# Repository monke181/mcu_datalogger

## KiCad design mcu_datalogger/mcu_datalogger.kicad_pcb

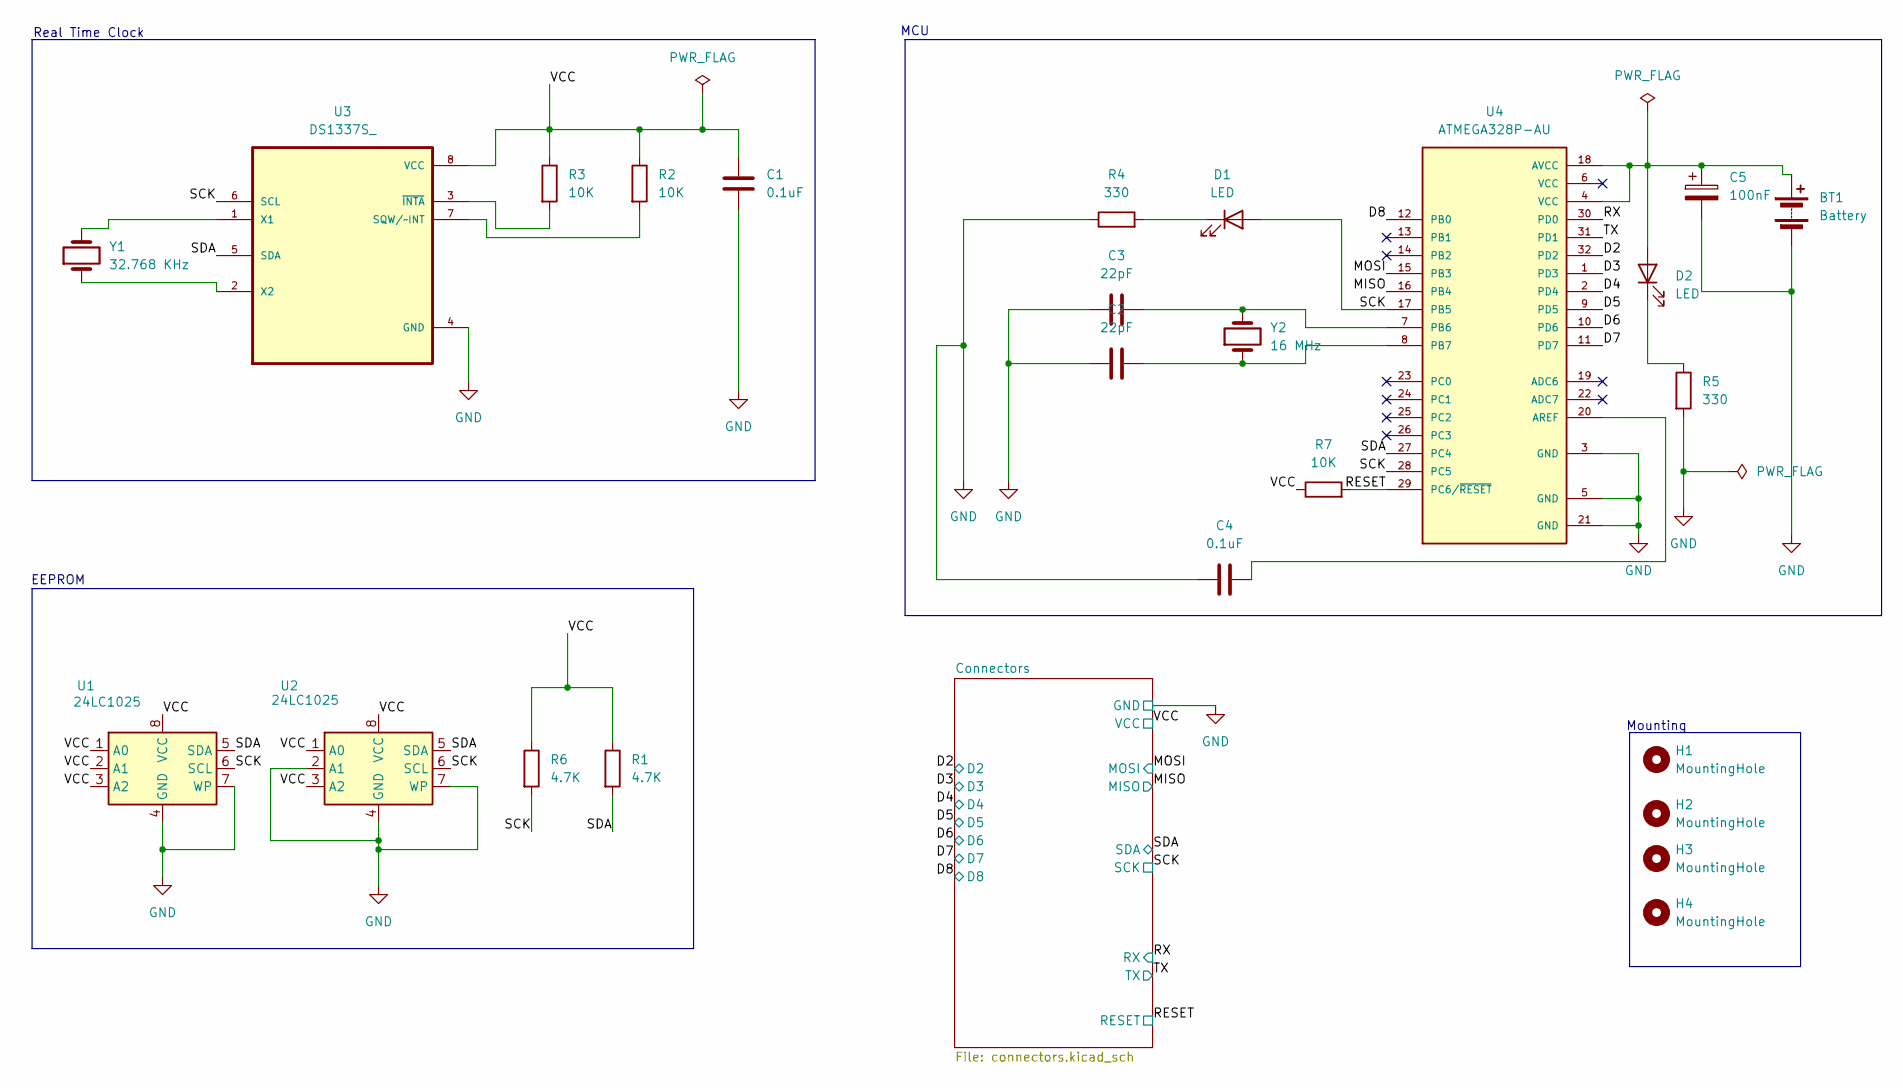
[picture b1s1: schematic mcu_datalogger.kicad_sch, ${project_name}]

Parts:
BT1: Battery; PinHeader_1x02_P2.54mm_Vertical
C1, C4: 0.1uF; C_0805_2012Metric
C2, C3: 22pF; C_0805_2012Metric
C5: 100nF; C_0805_2012Metric
D1, D2: LED; LED_0805_2012Metric
H1, H2, H3, H4: MountingHole; MountingHole_2.1mm
R1, R6: 4.7K; R_0805_2012Metric
R2, R3, R7: 10K; R_0805_2012Metric
R4, R5: 330; R_0805_2012Metric
U1, U2: 24LC1025; SOIC-8_3.9x4.9mm_P1.27mm
U3: DS1337S_; SOIC127P600X175-8N
U4: ATMEGA328P-AU; QFP80P900X900X120-32N; PARTREV 8271A
Y1: 32.768 KHz; Crystal_SMD_5032-2Pin_5.0x3.2mm_HandSoldering
Y2: 16 MHz; Crystal_SMD_5032-2Pin_5.0x3.2mm_HandSoldering

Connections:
/D2: U4.32 (PD2); also elsewhere on the board
/D3: U4.1 (PD3); also elsewhere on the board
/D4: U4.2 (PD4); also elsewhere on the board
/D5: U4.9 (PD5); also elsewhere on the board
/D6: U4.10 (PD6); also elsewhere on the board
/D7: U4.11 (PD7); also elsewhere on the board
/D8: U4.12 (PB0); also elsewhere on the board
/MISO: U4.16 (PB4); also elsewhere on the board
/MOSI: U4.15 (PB3); also elsewhere on the board
/RESET: R7.2, U4.29 (PC6/~RESET); also elsewhere on the board
/RX: U4.30 (PD0); also elsewhere on the board
/SCK: D1.2 (A), R6.2, U1.6 (SCL), U2.6 (SCL), U3.6 (SCL), U4.17 (PB5), U4.28 (PC5); also elsewhere on the board
/SDA: R1.2, U1.5 (SDA), U2.5 (SDA), U3.5 (SDA), U4.27 (PC4); also elsewhere on the board
/TX: U4.31 (PD1); also elsewhere on the board
/VCC: C1.1, R1.1, R2.1, R3.1, R6.1, R7.1, U1.1 (A0), U1.2 (A1), U1.3 (A2), U1.8 (VCC), U2.1 (A0), U2.3 (A2), U2.8 (VCC), U3.8 (VCC); also elsewhere on the board
GND: BT1.2 (-), C1.2, C2.1, C3.1, C4.2, C5.2, R4.1, R5.2, U1.4 (GND), U1.7 (WP), U2.2 (A1), U2.4 (GND), U2.7 (WP), U3.4 (GND), U4.3 (GND), U4.5 (GND), U4.21 (GND); also elsewhere on the board
unnamed: BT1.1 (+), C5.1, D2.2 (A), U4.4 (VCC), U4.18 (AVCC)
unnamed: D1.1 (K), R4.2
unnamed: D2.1 (K), R5.1
unnamed: R2.2, U3.7 (SQW/~INT)
unnamed: U3.1 (X1), Y1.2
unnamed: U3.2 (X2), Y1.1
unnamed: R3.2, U3.3 (~INTA)
unnamed: C4.1, U4.20 (AREF)
unnamed: C3.2, U4.7 (PB6), Y2.2
unnamed: C2.2, U4.8 (PB7), Y2.1

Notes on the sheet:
EEPROM
Real Time Clock
MCU
Mounting

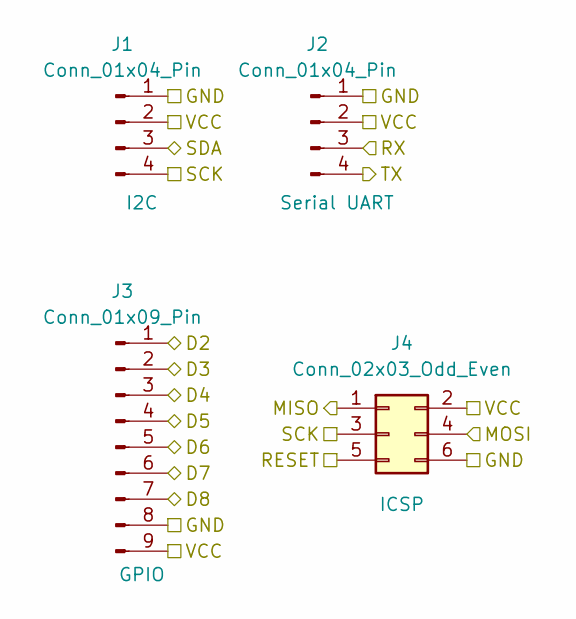
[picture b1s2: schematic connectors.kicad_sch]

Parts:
J1, J2: Conn_01x04_Pin; PinHeader_1x04_P2.54mm_Vertical
J3: Conn_01x09_Pin; PinHeader_1x09_P2.54mm_Vertical
J4: Conn_02x03_Odd_Even; PinHeader_2x03_P2.54mm_Vertical

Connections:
/D2: J3.1; also elsewhere on the board
/D3: J3.2; also elsewhere on the board
/D4: J3.3; also elsewhere on the board
/D5: J3.4; also elsewhere on the board
/D6: J3.5; also elsewhere on the board
/D7: J3.6; also elsewhere on the board
/D8: J3.7; also elsewhere on the board
/MISO: J4.1; also elsewhere on the board
/MOSI: J4.4; also elsewhere on the board
/RESET: J4.5; also elsewhere on the board
/RX: J2.3; also elsewhere on the board
/SCK: J1.4, J4.3; also elsewhere on the board
/SDA: J1.3; also elsewhere on the board
/TX: J2.4; also elsewhere on the board
/VCC: J1.2, J2.2, J3.9, J4.2; also elsewhere on the board
GND: J1.1, J2.1, J3.8, J4.6; also elsewhere on the board

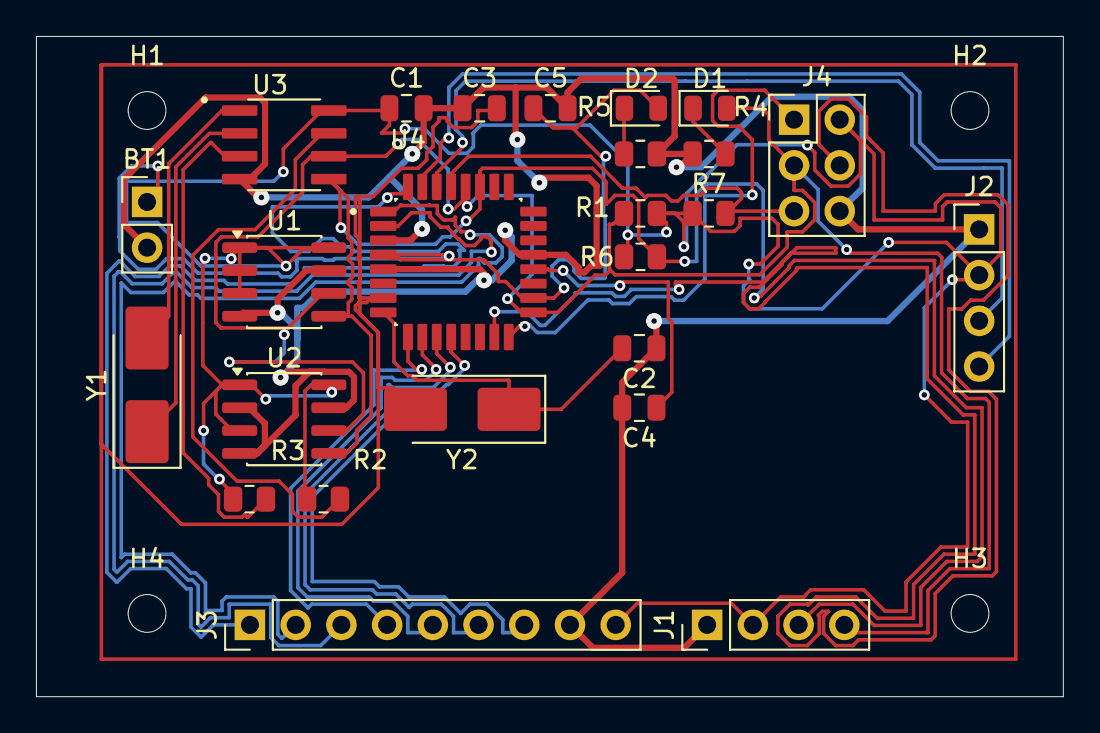
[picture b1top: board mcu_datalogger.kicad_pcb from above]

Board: 2 copper layers, 57.0 x 36.7 mm, 29 parts (0 on the bottom side), 26 nets.
